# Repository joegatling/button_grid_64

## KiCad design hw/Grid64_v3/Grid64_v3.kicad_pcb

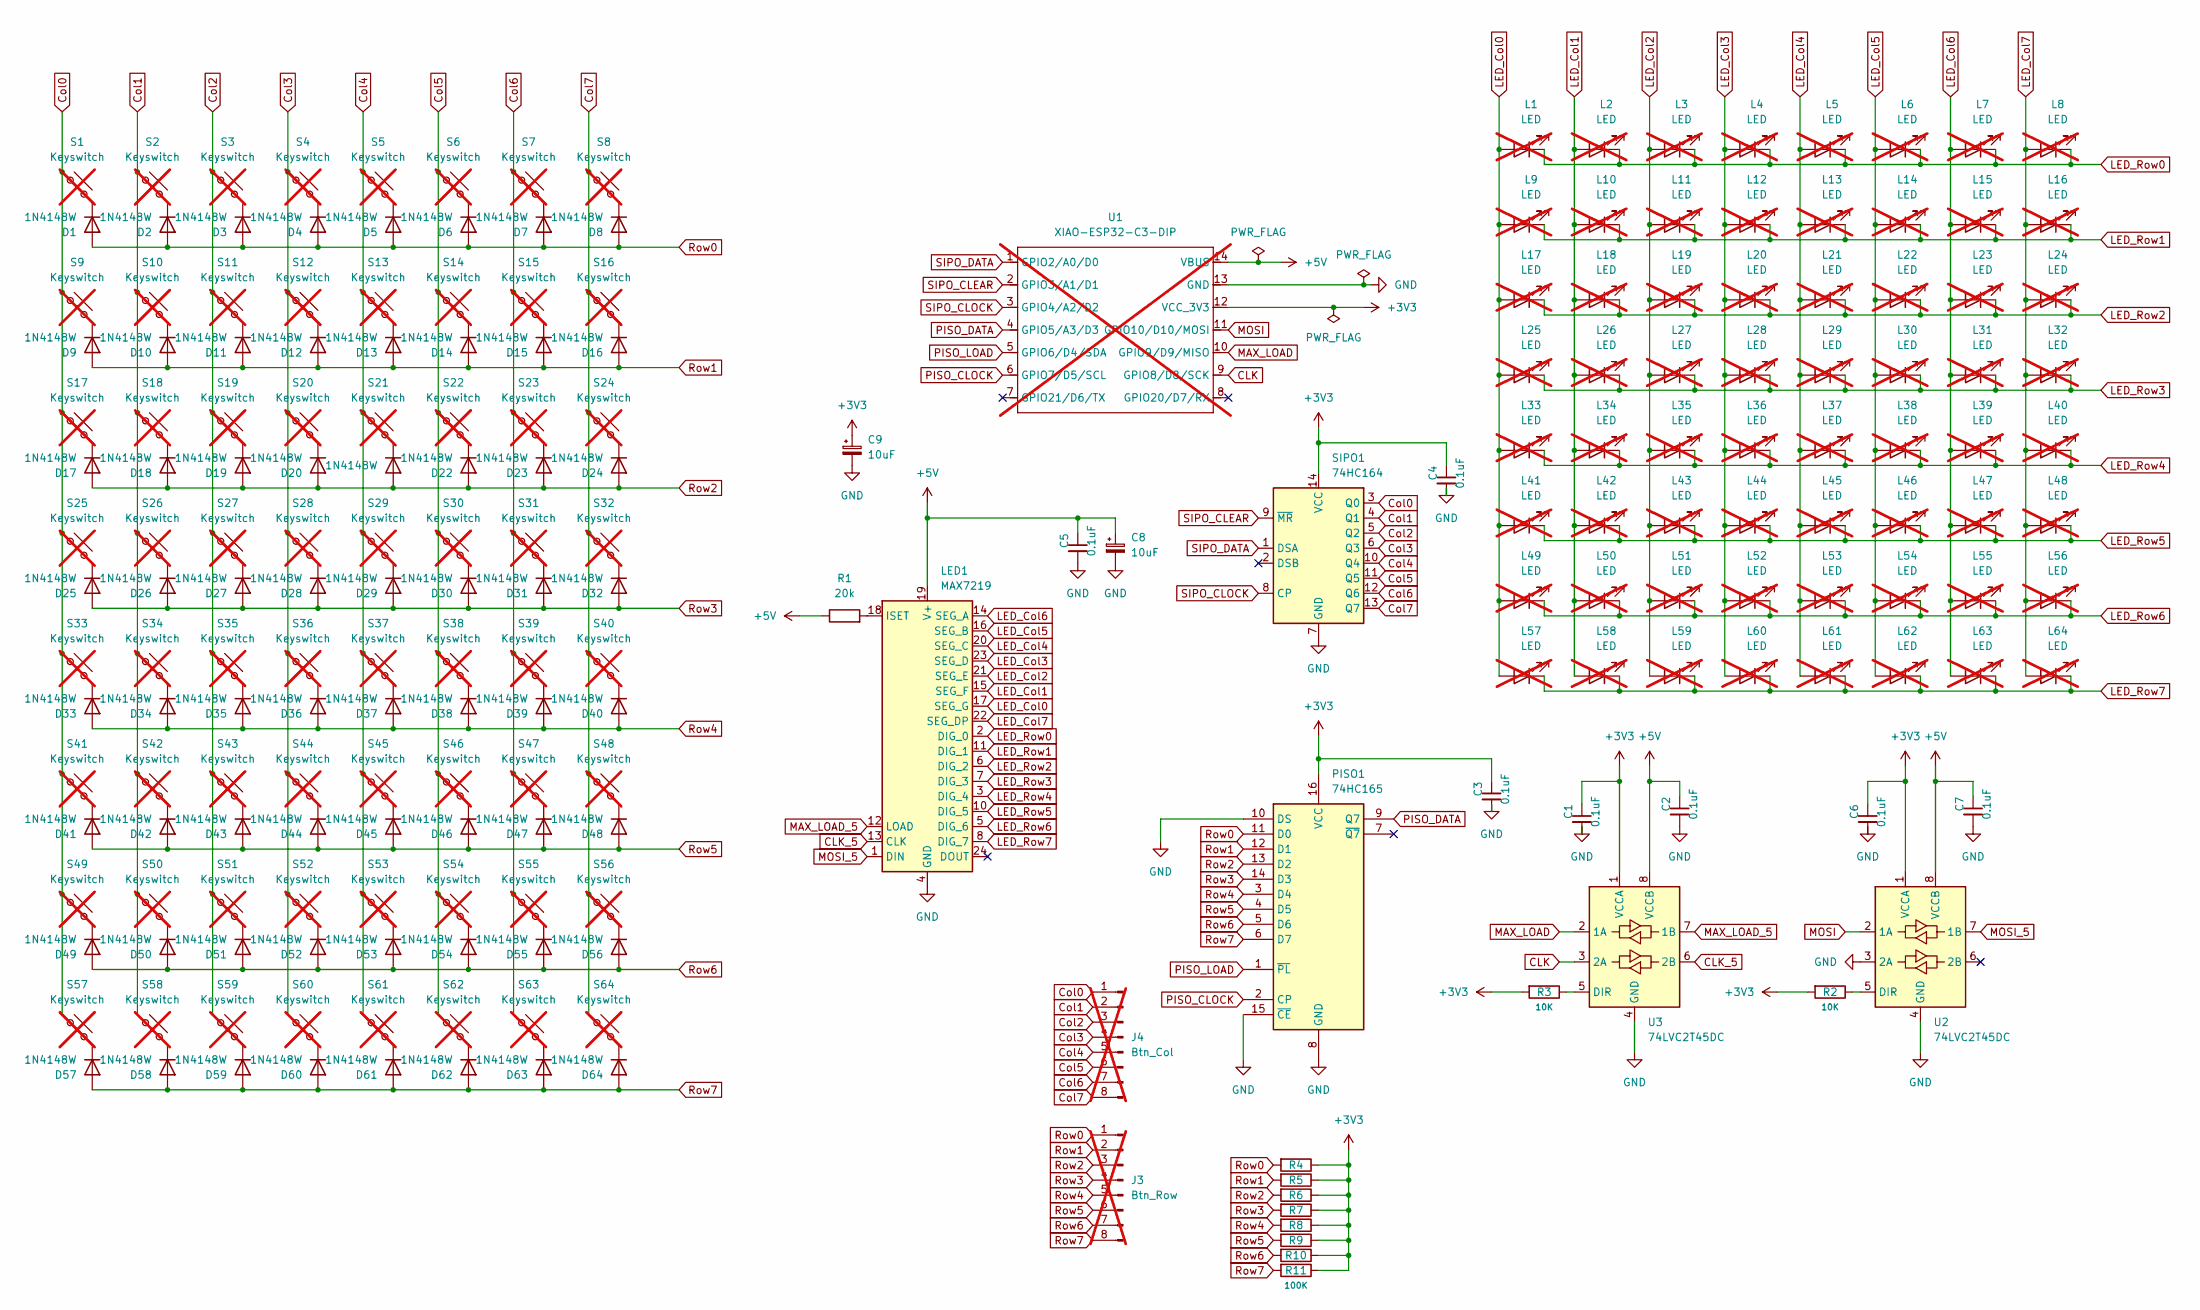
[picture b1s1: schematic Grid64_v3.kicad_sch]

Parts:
C1, C2, C3, C4, C5, C6, C7: 0.1uF; C_0805_2012Metric; LCSC C49678
C8, C9: 10uF; CP_Elec_4x5.3; LCSC C249692
D1, D2, D3, D4, D5, D6, D7, D8, D9, D10, D11, D12, D13, D14, D15, D16, D17, D18, D19, D20, D21, D22, D23, D24, D25, D26, D27, D28, D29, D30, D31, D32, D33, D34, D35, D36, D37, D38, D39, D40, D41, D42, D43, D44, D45, D46, D47, D48, D49, D50, D51, D52, D53, D54, D55, D56, D57, D58, D59, D60, D61, D62, D63, D64: 1N4148W; D_SOD-123
J3: Btn_Row; PinHeader_1x08_P1.00mm_Vertical; not fitted
J4: Btn_Col; PinHeader_1x08_P1.00mm_Vertical; not fitted
L1, L2, L3, L4, L5, L6, L7, L8, L9, L10, L11, L12, L13, L14, L15, L16, L17, L18, L19, L20, L21, L22, L23, L24, L25, L26, L27, L28, L29, L30, L31, L32, L33, L34, L35, L36, L37, L38, L39, L40, L41, L42, L43, L44, L45, L46, L47, L48, L49, L50, L51, L52, L53, L54, L55, L56, L57, L58, L59, L60, L61, L62, L63, L64: LED; MX-LED; not fitted
LED1: MAX7219; SOIC-24W_7.5x15.4mm_P1.27mm; LCSC C9964
PISO1: 74HC165; SOIC-16_3.9x9.9mm_P1.27mm; LCSC C5613
R1: 20k; R_0805_2012Metric
R2, R3: 10K; R_0805_2012Metric
R4, R5, R6, R7, R8, R9, R10, R11: 100K; R_0805_2012Metric
S1, S2, S3, S4, S5, S6, S7, S8, S9, S10, S11, S12, S13, S14, S15, S16, S17, S18, S19, S20, S21, S22, S23, S24, S25, S26, S27, S28, S29, S30, S31, S32, S33, S34, S35, S36, S37, S38, S39, S40, S41, S42, S43, S44, S45, S46, S47, S48, S49, S50, S51, S52, S53, S54, S55, S56, S57, S58, S59, S60, S61, S62, S63, S64: Keyswitch; MX-Solderable-1U_Mod; not fitted
SIPO1: 74HC164; SOIC-14_3.9x8.7mm_P1.27mm; LCSC C18164492
U1: XIAO-ESP32-C3-DIP; XIAO-ESP32C3-DIP; not fitted
U2, U3: 74LVC2T45DC; VSSOP-8_2.3x2mm_P0.5mm; LCSC C730237

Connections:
+3V3: C1.1, C3.1, C4.1, C6.1, C9.1, PISO1.16 (VCC), R2.2, R3.2, R4.1, R5.1, R6.1, R7.1, R8.1, R9.1, R10.1, R11.1, SIPO1.14 (VCC), U1.12 (VCC_3V3), U2.1 (VCCA), U3.1 (VCCA)
+5V: C2.1, C5.1, C7.1, C8.1, LED1.19 (V+), R1.1, U1.14 (VBUS), U2.8 (VCCB), U3.8 (VCCB)
CLK: U1.9 (GPIO8/D8/SCK), U3.3 (2A)
CLK_5: LED1.13 (CLK), U3.6 (2B)
Col0: J4.1, S1.1, S9.1, S17.1, S25.1, S33.1, S41.1, S49.1, S57.1, SIPO1.3 (Q0)
Col1: J4.2, S2.1, S10.1, S18.1, S26.1, S34.1, S42.1, S50.1, S58.1, SIPO1.4 (Q1)
Col2: J4.3, S3.1, S11.1, S19.1, S27.1, S35.1, S43.1, S51.1, S59.1, SIPO1.5 (Q2)
Col3: J4.4, S4.1, S12.1, S20.1, S28.1, S36.1, S44.1, S52.1, S60.1, SIPO1.6 (Q3)
Col4: J4.5, S5.1, S13.1, S21.1, S29.1, S37.1, S45.1, S53.1, S61.1, SIPO1.10 (Q4)
Col5: J4.6, S6.1, S14.1, S22.1, S30.1, S38.1, S46.1, S54.1, S62.1, SIPO1.11 (Q5)
Col6: J4.7, S7.1, S15.1, S23.1, S31.1, S39.1, S47.1, S55.1, S63.1, SIPO1.12 (Q6)
Col7: J4.8, S8.1, S16.1, S24.1, S32.1, S40.1, S48.1, S56.1, S64.1, SIPO1.13 (Q7)
GND: C1.2, C2.2, C3.2, C4.2, C5.2, C7.2, C8.2, C9.2, LED1.4 (GND), LED1.9 (GND), PISO1.8 (GND), PISO1.10 (DS), PISO1.15 (~CE), SIPO1.7 (GND), U1.13 (GND), U2.3 (2A), U2.4 (GND), U3.4 (GND)
LED_Col0: L1.2 (A), L9.2 (A), L17.2 (A), L25.2 (A), L33.2 (A), L41.2 (A), L49.2 (A), L57.2 (A), LED1.17 (SEG_G)
LED_Col1: L2.2 (A), L10.2 (A), L18.2 (A), L26.2 (A), L34.2 (A), L42.2 (A), L50.2 (A), L58.2 (A), LED1.15 (SEG_F)
LED_Col2: L3.2 (A), L11.2 (A), L19.2 (A), L27.2 (A), L35.2 (A), L43.2 (A), L51.2 (A), L59.2 (A), LED1.21 (SEG_E)
LED_Col3: L4.2 (A), L12.2 (A), L20.2 (A), L28.2 (A), L36.2 (A), L44.2 (A), L52.2 (A), L60.2 (A), LED1.23 (SEG_D)
LED_Col4: L5.2 (A), L13.2 (A), L21.2 (A), L29.2 (A), L37.2 (A), L45.2 (A), L53.2 (A), L61.2 (A), LED1.20 (SEG_C)
LED_Col5: L6.2 (A), L14.2 (A), L22.2 (A), L30.2 (A), L38.2 (A), L46.2 (A), L54.2 (A), L62.2 (A), LED1.16 (SEG_B)
LED_Col6: L7.2 (A), L15.2 (A), L23.2 (A), L31.2 (A), L39.2 (A), L47.2 (A), L55.2 (A), L63.2 (A), LED1.14 (SEG_A)
LED_Col7: L8.2 (A), L16.2 (A), L24.2 (A), L32.2 (A), L40.2 (A), L48.2 (A), L56.2 (A), L64.2 (A), LED1.22 (SEG_DP)
LED_Row0: L1.1 (K), L2.1 (K), L3.1 (K), L4.1 (K), L5.1 (K), L6.1 (K), L7.1 (K), L8.1 (K), LED1.2 (DIG_0)
LED_Row1: L9.1 (K), L10.1 (K), L11.1 (K), L12.1 (K), L13.1 (K), L14.1 (K), L15.1 (K), L16.1 (K), LED1.11 (DIG_1)
LED_Row2: L17.1 (K), L18.1 (K), L19.1 (K), L20.1 (K), L21.1 (K), L22.1 (K), L23.1 (K), L24.1 (K), LED1.6 (DIG_2)
LED_Row3: L25.1 (K), L26.1 (K), L27.1 (K), L28.1 (K), L29.1 (K), L30.1 (K), L31.1 (K), L32.1 (K), LED1.7 (DIG_3)
LED_Row4: L33.1 (K), L34.1 (K), L35.1 (K), L36.1 (K), L37.1 (K), L38.1 (K), L39.1 (K), L40.1 (K), LED1.3 (DIG_4)
LED_Row5: L41.1 (K), L42.1 (K), L43.1 (K), L44.1 (K), L45.1 (K), L46.1 (K), L47.1 (K), L48.1 (K), LED1.10 (DIG_5)
LED_Row6: L49.1 (K), L50.1 (K), L51.1 (K), L52.1 (K), L53.1 (K), L54.1 (K), L55.1 (K), L56.1 (K), LED1.5 (DIG_6)
LED_Row7: L57.1 (K), L58.1 (K), L59.1 (K), L60.1 (K), L61.1 (K), L62.1 (K), L63.1 (K), L64.1 (K), LED1.8 (DIG_7)
MAX_LOAD: U1.10 (GPIO9/D9/MISO), U3.2 (1A)
MAX_LOAD_5: LED1.12 (LOAD), U3.7 (1B)
MOSI: U1.11 (GPIO10/D10/MOSI), U2.2 (1A)
MOSI_5: LED1.1 (DIN), U2.7 (1B)
unnamed: D1.1 (K), S1.2
unnamed: D2.1 (K), S2.2
unnamed: D3.1 (K), S3.2
unnamed: D4.1 (K), S4.2
unnamed: D5.1 (K), S5.2
unnamed: D6.1 (K), S6.2
unnamed: D7.1 (K), S7.2
unnamed: D8.1 (K), S8.2
unnamed: D9.1 (K), S9.2
unnamed: D10.1 (K), S10.2
unnamed: D11.1 (K), S11.2
unnamed: D12.1 (K), S12.2
unnamed: D13.1 (K), S13.2
unnamed: D14.1 (K), S14.2
unnamed: D15.1 (K), S15.2
unnamed: D16.1 (K), S16.2
unnamed: D17.1 (K), S17.2
unnamed: D18.1 (K), S18.2
unnamed: D19.1 (K), S19.2
unnamed: D20.1 (K), S20.2
unnamed: D21.1 (K), S21.2
unnamed: D22.1 (K), S22.2
unnamed: D23.1 (K), S23.2
unnamed: D24.1 (K), S24.2
unnamed: D25.1 (K), S25.2
unnamed: D26.1 (K), S26.2
unnamed: D27.1 (K), S27.2
unnamed: D28.1 (K), S28.2
unnamed: D29.1 (K), S29.2
unnamed: D30.1 (K), S30.2
unnamed: D31.1 (K), S31.2
unnamed: D32.1 (K), S32.2
unnamed: D33.1 (K), S33.2
unnamed: D34.1 (K), S34.2
unnamed: D35.1 (K), S35.2
unnamed: D36.1 (K), S36.2
unnamed: D37.1 (K), S37.2
unnamed: D38.1 (K), S38.2
unnamed: D39.1 (K), S39.2
unnamed: D40.1 (K), S40.2
unnamed: D41.1 (K), S41.2
unnamed: D42.1 (K), S42.2
unnamed: D43.1 (K), S43.2
unnamed: D44.1 (K), S44.2
unnamed: D45.1 (K), S45.2
unnamed: D46.1 (K), S46.2
unnamed: D47.1 (K), S47.2
unnamed: D48.1 (K), S48.2
unnamed: D49.1 (K), S49.2
unnamed: D50.1 (K), S50.2
unnamed: D51.1 (K), S51.2
unnamed: D52.1 (K), S52.2
unnamed: D53.1 (K), S53.2
unnamed: D54.1 (K), S54.2
unnamed: D55.1 (K), S55.2
unnamed: D56.1 (K), S56.2
unnamed: D57.1 (K), S57.2
unnamed: D58.1 (K), S58.2
unnamed: D59.1 (K), S59.2
unnamed: D60.1 (K), S60.2
unnamed: D61.1 (K), S61.2
unnamed: D62.1 (K), S62.2
unnamed: D63.1 (K), S63.2
unnamed: D64.1 (K), S64.2
unnamed: LED1.18 (ISET), R1.2
unnamed: R2.1, U2.5 (DIR)
unnamed: R3.1, U3.5 (DIR)
PISO_CLOCK: PISO1.2 (CP), U1.6 (GPIO7/D5/SCL)
PISO_DATA: PISO1.9 (Q7), U1.4 (GPIO5/A3/D3)
PISO_LOAD: PISO1.1 (~PL), U1.5 (GPIO6/D4/SDA)
Row0: D1.2 (A), D2.2 (A), D3.2 (A), D4.2 (A), D5.2 (A), D6.2 (A), D7.2 (A), D8.2 (A), J3.1, PISO1.11 (D0), R4.2
Row1: D9.2 (A), D10.2 (A), D11.2 (A), D12.2 (A), D13.2 (A), D14.2 (A), D15.2 (A), D16.2 (A), J3.2, PISO1.12 (D1), R5.2
Row2: D17.2 (A), D18.2 (A), D19.2 (A), D20.2 (A), D21.2 (A), D22.2 (A), D23.2 (A), D24.2 (A), J3.3, PISO1.13 (D2), R6.2
Row3: D25.2 (A), D26.2 (A), D27.2 (A), D28.2 (A), D29.2 (A), D30.2 (A), D31.2 (A), D32.2 (A), J3.4, PISO1.14 (D3), R7.2
Row4: D33.2 (A), D34.2 (A), D35.2 (A), D36.2 (A), D37.2 (A), D38.2 (A), D39.2 (A), D40.2 (A), J3.5, PISO1.3 (D4), R8.2
Row5: D41.2 (A), D42.2 (A), D43.2 (A), D44.2 (A), D45.2 (A), D46.2 (A), D47.2 (A), D48.2 (A), J3.6, PISO1.4 (D5), R9.2
Row6: D49.2 (A), D50.2 (A), D51.2 (A), D52.2 (A), D53.2 (A), D54.2 (A), D55.2 (A), D56.2 (A), J3.7, PISO1.5 (D6), R10.2
Row7: D57.2 (A), D58.2 (A), D59.2 (A), D60.2 (A), D61.2 (A), D62.2 (A), D63.2 (A), D64.2 (A), J3.8, PISO1.6 (D7), R11.2
SIPO_CLEAR: SIPO1.9 (~MR), U1.2 (GPIO3/A1/D1)
SIPO_CLOCK: SIPO1.8 (CP), U1.3 (GPIO4/A2/D2)
SIPO_DATA: SIPO1.1 (DSA), U1.1 (GPIO2/A0/D0)

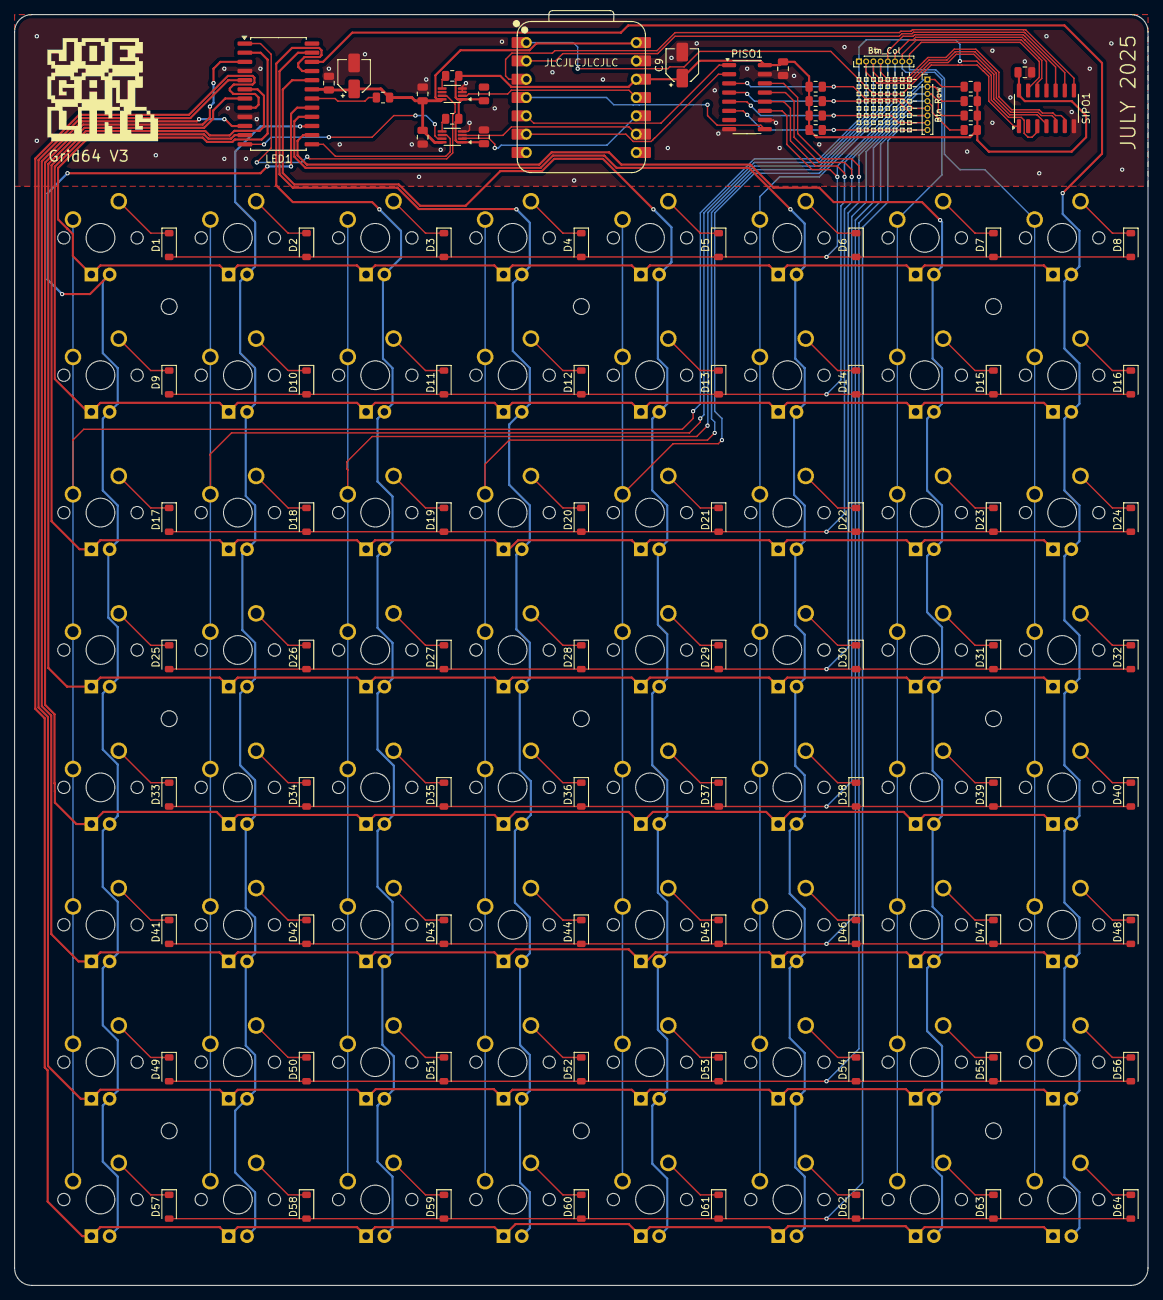
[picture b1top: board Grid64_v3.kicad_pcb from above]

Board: 2 copper layers, 157.2 x 176.2 mm, 229 parts (0 on the bottom side), 114 nets.

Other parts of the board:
H1, H2, H3, H4, H5, H6, H7, H8, H9: MountingHole_2.2mm_M2

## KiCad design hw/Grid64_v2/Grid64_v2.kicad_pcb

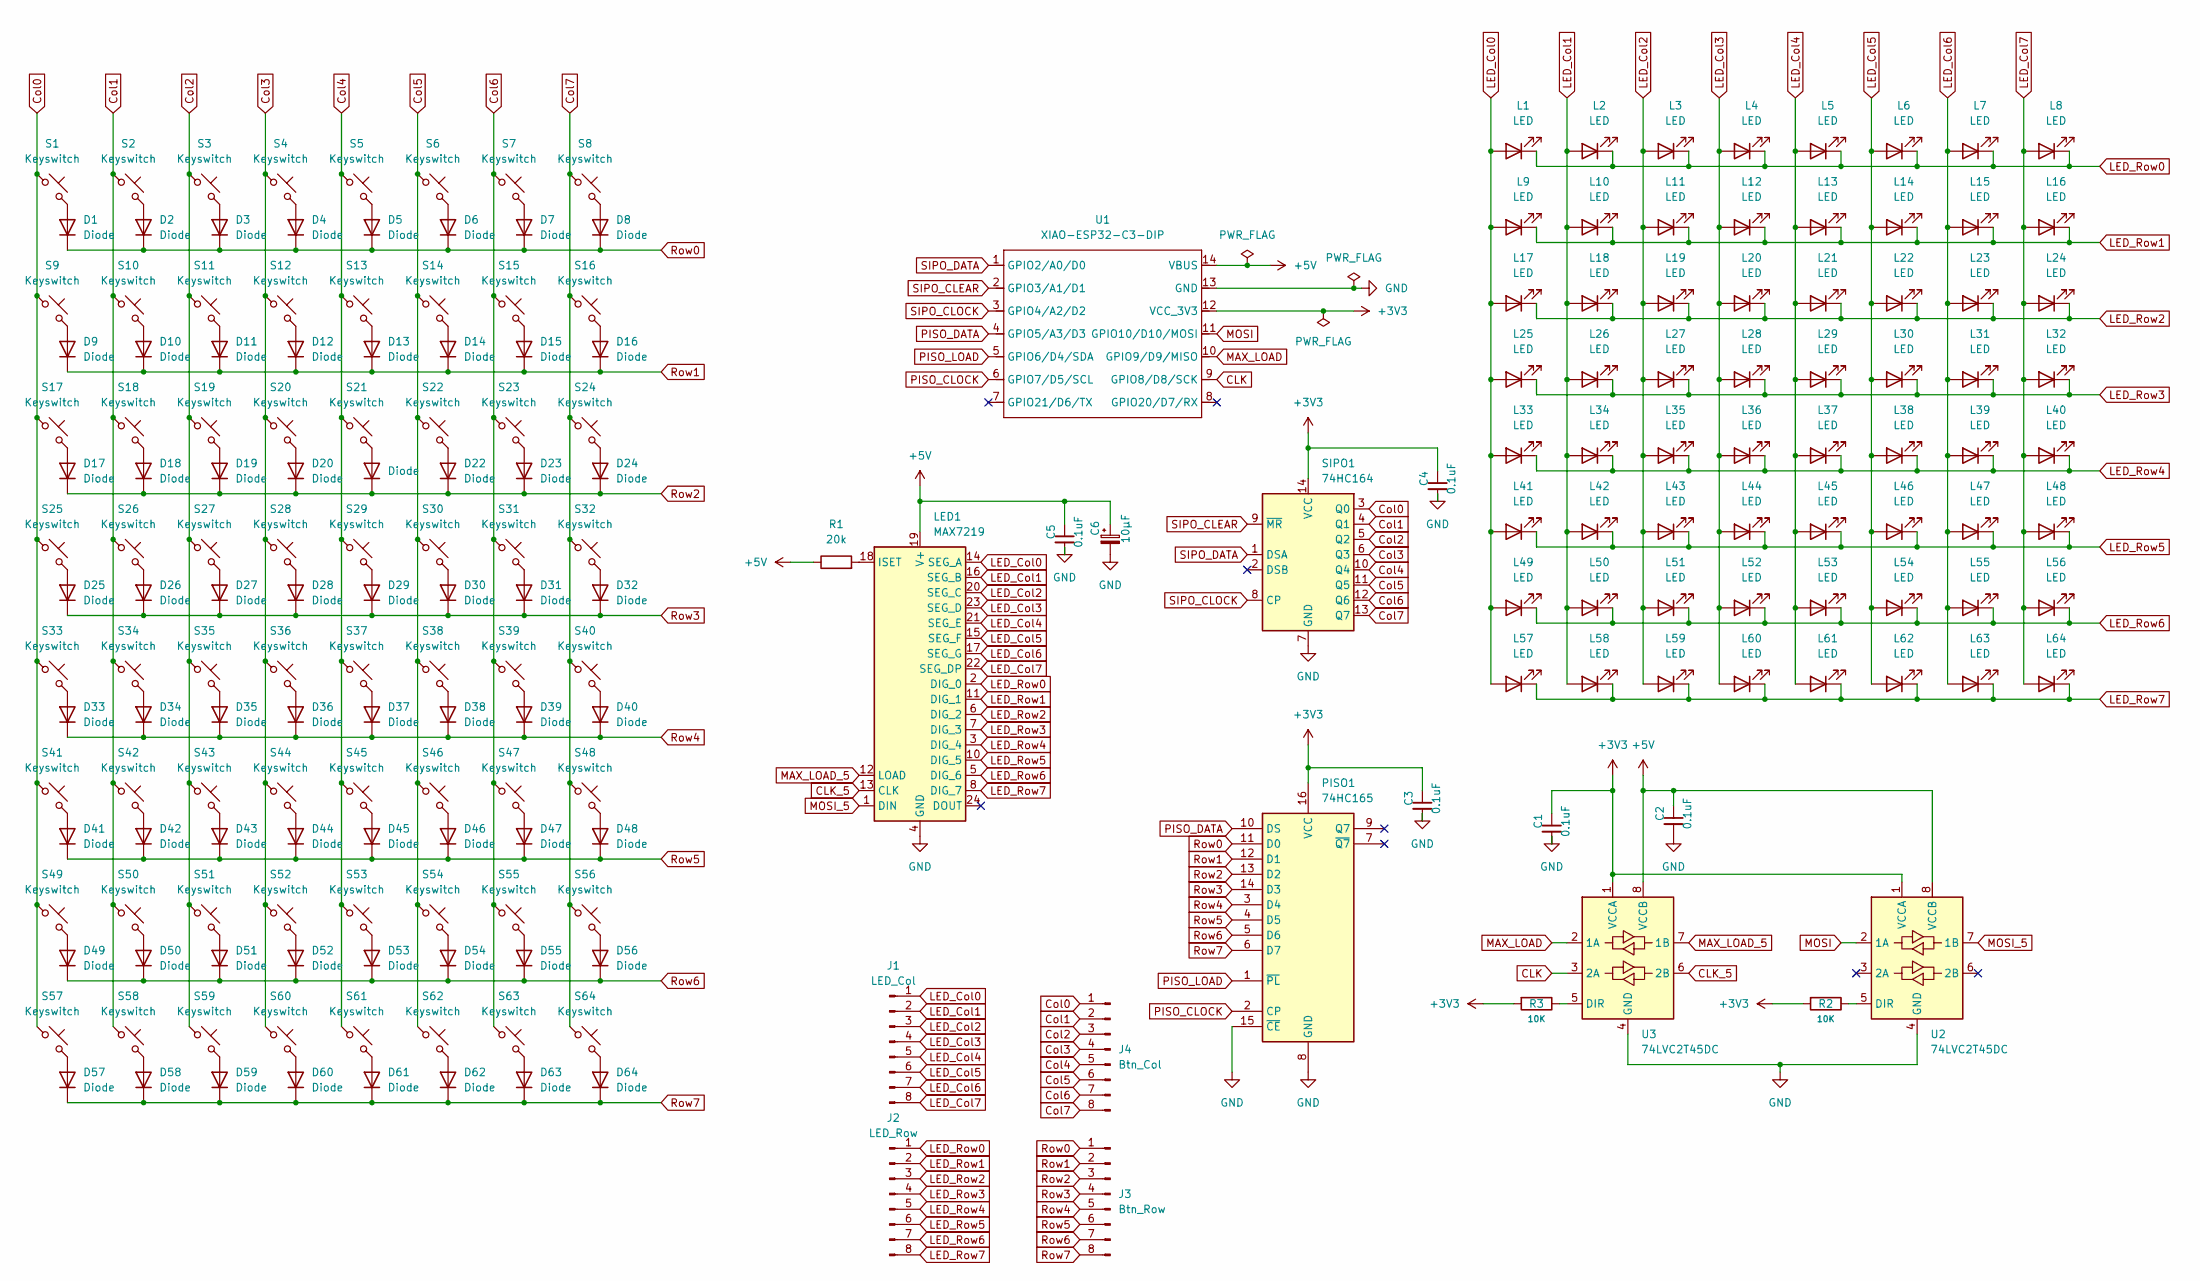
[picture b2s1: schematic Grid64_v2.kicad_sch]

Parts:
C1, C2, C3, C4, C5: 0.1uF; C_0805_2012Metric
C6: 10μF; C_Elec_3x5.4
D1, D2, D3, D4, D5, D6, D7, D8, D9, D10, D11, D12, D13, D14, D15, D16, D17, D18, D19, D20, D21, D22, D23, D24, D25, D26, D27, D28, D29, D30, D31, D32, D33, D34, D35, D36, D37, D38, D39, D40, D41, D42, D43, D44, D45, D46, D47, D48, D49, D50, D51, D52, D53, D54, D55, D56, D57, D58, D59, D60, D61, D62, D63, D64: Diode; D_SOD-123
J1: LED_Col; PinHeader_1x08_P1.00mm_Vertical
J2: LED_Row; PinHeader_1x08_P1.00mm_Vertical
J3: Btn_Row; PinHeader_1x08_P1.00mm_Vertical
J4: Btn_Col; PinHeader_1x08_P1.00mm_Vertical
L1: LED; MX-LED-PolarityMarked
L2, L3, L4, L5, L6, L7, L8, L9, L10, L11, L12, L13, L14, L15, L16, L17, L18, L19, L20, L21, L22, L23, L24, L25, L26, L27, L28, L29, L30, L31, L32, L33, L34, L35, L36, L37, L38, L39, L40, L41, L42, L43, L44, L45, L46, L47, L48, L49, L50, L51, L52, L53, L54, L55, L56, L57, L58, L59, L60, L61, L62, L63, L64: LED; MX-LED
LED1: MAX7219; SOIC-24W_7.5x15.4mm_P1.27mm
PISO1: 74HC165; SOIC-16_3.9x9.9mm_P1.27mm
R1: 20k; R_0805_2012Metric
R2, R3: 10K; R_0805_2012Metric
S1, S2, S3, S4, S5, S6, S7, S8, S9, S10, S11, S12, S13, S14, S15, S16, S17, S18, S19, S20, S21, S22, S23, S24, S25, S26, S27, S28, S29, S30, S31, S32, S33, S34, S35, S36, S37, S38, S39, S40, S41, S42, S43, S44, S45, S46, S47, S48, S49, S50, S51, S52, S53, S54, S55, S56, S57, S58, S59, S60, S61, S62, S63, S64: Keyswitch; MX-Solderable-1U_Mod
SIPO1: 74HC164; SOIC-14_3.9x8.7mm_P1.27mm
U1: XIAO-ESP32-C3-DIP; XIAO-ESP32C3-DIP
U2, U3: 74LVC2T45DC; VSSOP-8_2.3x2mm_P0.5mm

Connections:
+3V3: C1.1, C3.1, C4.1, PISO1.16 (VCC), R2.2, R3.2, SIPO1.14 (VCC), U1.12 (VCC_3V3), U2.1 (VCCA), U3.1 (VCCA)
+5V: C2.1, C5.1, C6.1, LED1.19 (V+), R1.1, U1.14 (VBUS), U2.8 (VCCB), U3.8 (VCCB)
CLK: U1.9 (GPIO8/D8/SCK), U3.3 (2A)
CLK_5: LED1.13 (CLK), U3.6 (2B)
Col0: J4.1, S1.1, S9.1, S17.1, S25.1, S33.1, S41.1, S49.1, S57.1, SIPO1.3 (Q0)
Col1: J4.2, S2.1, S10.1, S18.1, S26.1, S34.1, S42.1, S50.1, S58.1, SIPO1.4 (Q1)
Col2: J4.3, S3.1, S11.1, S19.1, S27.1, S35.1, S43.1, S51.1, S59.1, SIPO1.5 (Q2)
Col3: J4.4, S4.1, S12.1, S20.1, S28.1, S36.1, S44.1, S52.1, S60.1, SIPO1.6 (Q3)
Col4: J4.5, S5.1, S13.1, S21.1, S29.1, S37.1, S45.1, S53.1, S61.1, SIPO1.10 (Q4)
Col5: J4.6, S6.1, S14.1, S22.1, S30.1, S38.1, S46.1, S54.1, S62.1, SIPO1.11 (Q5)
Col6: J4.7, S7.1, S15.1, S23.1, S31.1, S39.1, S47.1, S55.1, S63.1, SIPO1.12 (Q6)
Col7: J4.8, S8.1, S16.1, S24.1, S32.1, S40.1, S48.1, S56.1, S64.1, SIPO1.13 (Q7)
GND: C1.2, C2.2, C3.2, C4.2, C5.2, C6.2, LED1.4 (GND), LED1.9 (GND), PISO1.8 (GND), PISO1.15 (~CE), SIPO1.7 (GND), U1.13 (GND), U2.4 (GND), U3.4 (GND)
LED_Col0: J1.1, L1.2 (A), L9.2 (A), L17.2 (A), L25.2 (A), L33.2 (A), L41.2 (A), L49.2 (A), L57.2 (A), LED1.14 (SEG_A)
LED_Col1: J1.2, L2.2 (A), L10.2 (A), L18.2 (A), L26.2 (A), L34.2 (A), L42.2 (A), L50.2 (A), L58.2 (A), LED1.16 (SEG_B)
LED_Col2: J1.3, L3.2 (A), L11.2 (A), L19.2 (A), L27.2 (A), L35.2 (A), L43.2 (A), L51.2 (A), L59.2 (A), LED1.20 (SEG_C)
LED_Col3: J1.4, L4.2 (A), L12.2 (A), L20.2 (A), L28.2 (A), L36.2 (A), L44.2 (A), L52.2 (A), L60.2 (A), LED1.23 (SEG_D)
LED_Col4: J1.5, L5.2 (A), L13.2 (A), L21.2 (A), L29.2 (A), L37.2 (A), L45.2 (A), L53.2 (A), L61.2 (A), LED1.21 (SEG_E)
LED_Col5: J1.6, L6.2 (A), L14.2 (A), L22.2 (A), L30.2 (A), L38.2 (A), L46.2 (A), L54.2 (A), L62.2 (A), LED1.15 (SEG_F)
LED_Col6: J1.7, L7.2 (A), L15.2 (A), L23.2 (A), L31.2 (A), L39.2 (A), L47.2 (A), L55.2 (A), L63.2 (A), LED1.17 (SEG_G)
LED_Col7: J1.8, L8.2 (A), L16.2 (A), L24.2 (A), L32.2 (A), L40.2 (A), L48.2 (A), L56.2 (A), L64.2 (A), LED1.22 (SEG_DP)
LED_Row0: J2.1, L1.1 (K), L2.1 (K), L3.1 (K), L4.1 (K), L5.1 (K), L6.1 (K), L7.1 (K), L8.1 (K), LED1.2 (DIG_0)
LED_Row1: J2.2, L9.1 (K), L10.1 (K), L11.1 (K), L12.1 (K), L13.1 (K), L14.1 (K), L15.1 (K), L16.1 (K), LED1.11 (DIG_1)
LED_Row2: J2.3, L17.1 (K), L18.1 (K), L19.1 (K), L20.1 (K), L21.1 (K), L22.1 (K), L23.1 (K), L24.1 (K), LED1.6 (DIG_2)
LED_Row3: J2.4, L25.1 (K), L26.1 (K), L27.1 (K), L28.1 (K), L29.1 (K), L30.1 (K), L31.1 (K), L32.1 (K), LED1.7 (DIG_3)
LED_Row4: J2.5, L33.1 (K), L34.1 (K), L35.1 (K), L36.1 (K), L37.1 (K), L38.1 (K), L39.1 (K), L40.1 (K), LED1.3 (DIG_4)
LED_Row5: J2.6, L41.1 (K), L42.1 (K), L43.1 (K), L44.1 (K), L45.1 (K), L46.1 (K), L47.1 (K), L48.1 (K), LED1.10 (DIG_5)
LED_Row6: J2.7, L49.1 (K), L50.1 (K), L51.1 (K), L52.1 (K), L53.1 (K), L54.1 (K), L55.1 (K), L56.1 (K), LED1.5 (DIG_6)
LED_Row7: J2.8, L57.1 (K), L58.1 (K), L59.1 (K), L60.1 (K), L61.1 (K), L62.1 (K), L63.1 (K), L64.1 (K), LED1.8 (DIG_7)
MAX_LOAD: U1.10 (GPIO9/D9/MISO), U3.2 (1A)
MAX_LOAD_5: LED1.12 (LOAD), U3.7 (1B)
MOSI: U1.11 (GPIO10/D10/MOSI), U2.2 (1A)
MOSI_5: LED1.1 (DIN), U2.7 (1B)
unnamed: D1.2 (A), S1.2
unnamed: D2.2 (A), S2.2
unnamed: D3.2 (A), S3.2
unnamed: D4.2 (A), S4.2
unnamed: D5.2 (A), S5.2
unnamed: D6.2 (A), S6.2
unnamed: D7.2 (A), S7.2
unnamed: D8.2 (A), S8.2
unnamed: D9.2 (A), S9.2
unnamed: D10.2 (A), S10.2
unnamed: D11.2 (A), S11.2
unnamed: D12.2 (A), S12.2
unnamed: D13.2 (A), S13.2
unnamed: D14.2 (A), S14.2
unnamed: D15.2 (A), S15.2
unnamed: D16.2 (A), S16.2
unnamed: D17.2 (A), S17.2
unnamed: D18.2 (A), S18.2
unnamed: D19.2 (A), S19.2
unnamed: D20.2 (A), S20.2
unnamed: D21.2 (A), S21.2
unnamed: D22.2 (A), S22.2
unnamed: D23.2 (A), S23.2
unnamed: D24.2 (A), S24.2
unnamed: D25.2 (A), S25.2
unnamed: D26.2 (A), S26.2
unnamed: D27.2 (A), S27.2
unnamed: D28.2 (A), S28.2
unnamed: D29.2 (A), S29.2
unnamed: D30.2 (A), S30.2
unnamed: D31.2 (A), S31.2
unnamed: D32.2 (A), S32.2
unnamed: D33.2 (A), S33.2
unnamed: D34.2 (A), S34.2
unnamed: D35.2 (A), S35.2
unnamed: D36.2 (A), S36.2
unnamed: D37.2 (A), S37.2
unnamed: D38.2 (A), S38.2
unnamed: D39.2 (A), S39.2
unnamed: D40.2 (A), S40.2
unnamed: D41.2 (A), S41.2
unnamed: D42.2 (A), S42.2
unnamed: D43.2 (A), S43.2
unnamed: D44.2 (A), S44.2
unnamed: D45.2 (A), S45.2
unnamed: D46.2 (A), S46.2
unnamed: D47.2 (A), S47.2
unnamed: D48.2 (A), S48.2
unnamed: D49.2 (A), S49.2
unnamed: D50.2 (A), S50.2
unnamed: D51.2 (A), S51.2
unnamed: D52.2 (A), S52.2
unnamed: D53.2 (A), S53.2
unnamed: D54.2 (A), S54.2
unnamed: D55.2 (A), S55.2
unnamed: D56.2 (A), S56.2
unnamed: D57.2 (A), S57.2
unnamed: D58.2 (A), S58.2
unnamed: D59.2 (A), S59.2
unnamed: D60.2 (A), S60.2
unnamed: D61.2 (A), S61.2
unnamed: D62.2 (A), S62.2
unnamed: D63.2 (A), S63.2
unnamed: D64.2 (A), S64.2
unnamed: LED1.18 (ISET), R1.2
unnamed: R2.1, U2.5 (DIR)
unnamed: R3.1, U3.5 (DIR)
PISO_CLOCK: PISO1.2 (CP), U1.6 (GPIO7/D5/SCL)
PISO_DATA: PISO1.10 (DS), U1.4 (GPIO5/A3/D3)
PISO_LOAD: PISO1.1 (~PL), U1.5 (GPIO6/D4/SDA)
Row0: D1.1 (K), D2.1 (K), D3.1 (K), D4.1 (K), D5.1 (K), D6.1 (K), D7.1 (K), D8.1 (K), J3.1, PISO1.11 (D0)
Row1: D9.1 (K), D10.1 (K), D11.1 (K), D12.1 (K), D13.1 (K), D14.1 (K), D15.1 (K), D16.1 (K), J3.2, PISO1.12 (D1)
Row2: D17.1 (K), D18.1 (K), D19.1 (K), D20.1 (K), D21.1 (K), D22.1 (K), D23.1 (K), D24.1 (K), J3.3, PISO1.13 (D2)
Row3: D25.1 (K), D26.1 (K), D27.1 (K), D28.1 (K), D29.1 (K), D30.1 (K), D31.1 (K), D32.1 (K), J3.4, PISO1.14 (D3)
Row4: D33.1 (K), D34.1 (K), D35.1 (K), D36.1 (K), D37.1 (K), D38.1 (K), D39.1 (K), D40.1 (K), J3.5, PISO1.3 (D4)
Row5: D41.1 (K), D42.1 (K), D43.1 (K), D44.1 (K), D45.1 (K), D46.1 (K), D47.1 (K), D48.1 (K), J3.6, PISO1.4 (D5)
Row6: D49.1 (K), D50.1 (K), D51.1 (K), D52.1 (K), D53.1 (K), D54.1 (K), D55.1 (K), D56.1 (K), J3.7, PISO1.5 (D6)
Row7: D57.1 (K), D58.1 (K), D59.1 (K), D60.1 (K), D61.1 (K), D62.1 (K), D63.1 (K), D64.1 (K), J3.8, PISO1.6 (D7)
SIPO_CLEAR: SIPO1.9 (~MR), U1.2 (GPIO3/A1/D1)
SIPO_CLOCK: SIPO1.8 (CP), U1.3 (GPIO4/A2/D2)
SIPO_DATA: SIPO1.1 (DSA), U1.1 (GPIO2/A0/D0)

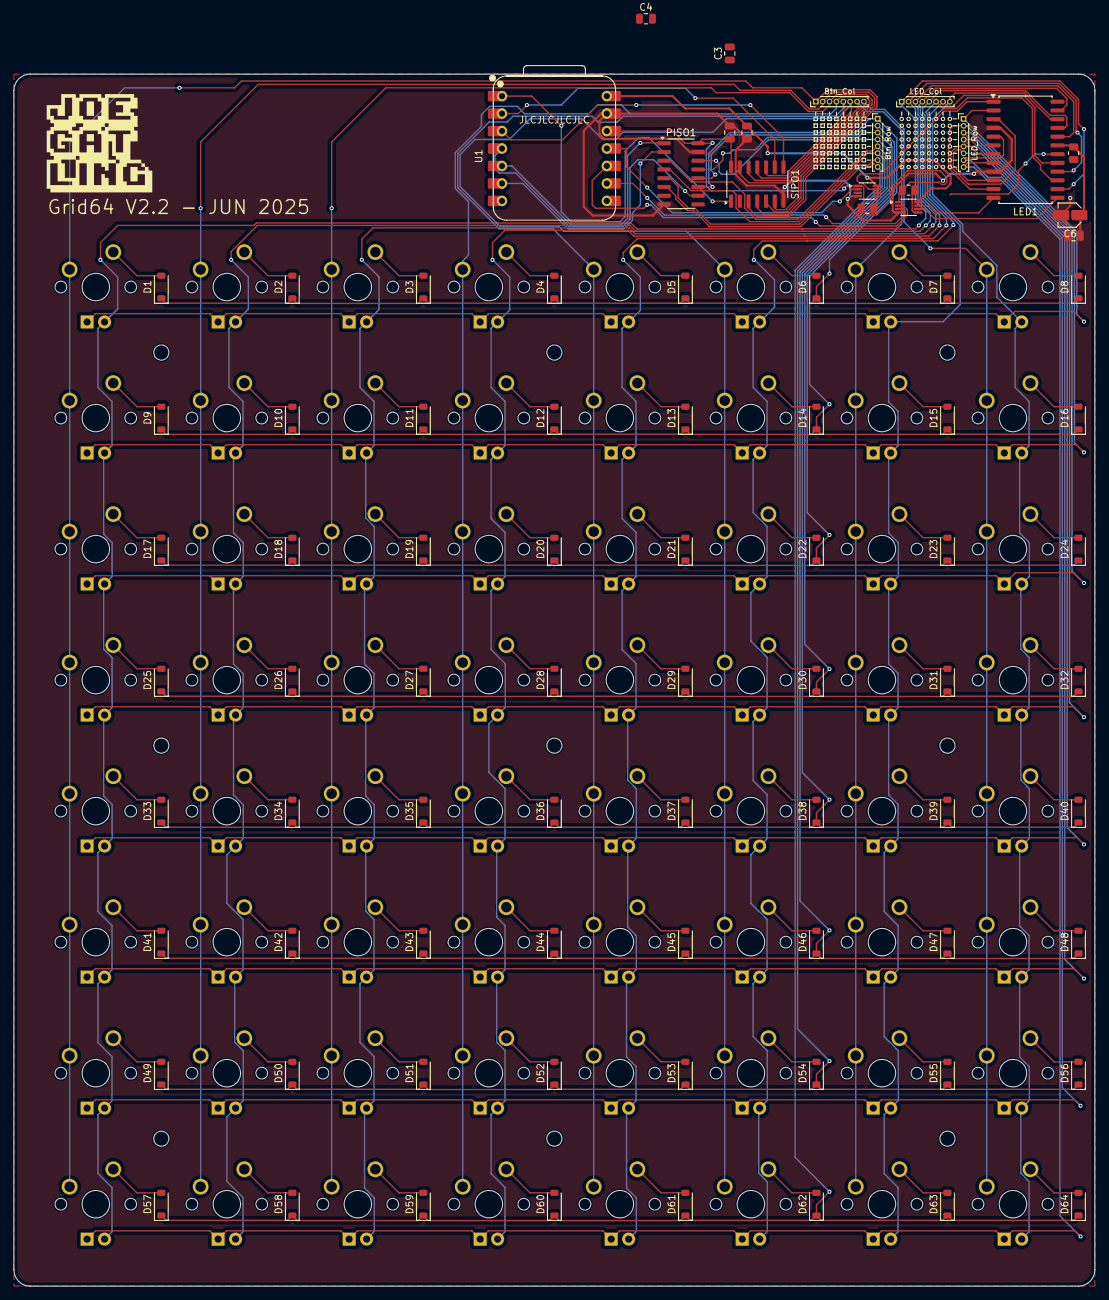
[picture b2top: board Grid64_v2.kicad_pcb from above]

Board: 2 copper layers, 157.2 x 176.2 mm, 220 parts (0 on the bottom side), 114 nets.

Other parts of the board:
H1, H2, H3, H4, H5, H6, H7, H8, H9: MountingHole_2.2mm_M2

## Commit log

2025-06-30 lots of hardware stuff
2025-07-11 Fixing the firmware and the hardware
2025-07-12 Lots of firmware improvements
